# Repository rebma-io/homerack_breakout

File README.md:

# STM32 Morpho Expansion Board for HOMERACK

Not really ready to talk about the project, but it was inspired by the
[kha](https://github.com/kiu/kha) project by WHO? This is just the beginning of the project, but I
decided to start with a STM32 Nucleo-64 board and work from there. This
is just a breakout for a bunch of the IO to a lot of JST PH connectors.

You can see the schematic and PCB layout
[online](https://kicanvas.org/?github=https%3A%2F%2Fgithub.com%2Frebma-io%2Fhomerack_breakout)
thanks to the super-brilliant [Stargirl](https://github.com/theacodes).

## License
The license is [CC0](https://creativecommons.org/public-domain/cc0/),
which means, effectively, do whatever you want.

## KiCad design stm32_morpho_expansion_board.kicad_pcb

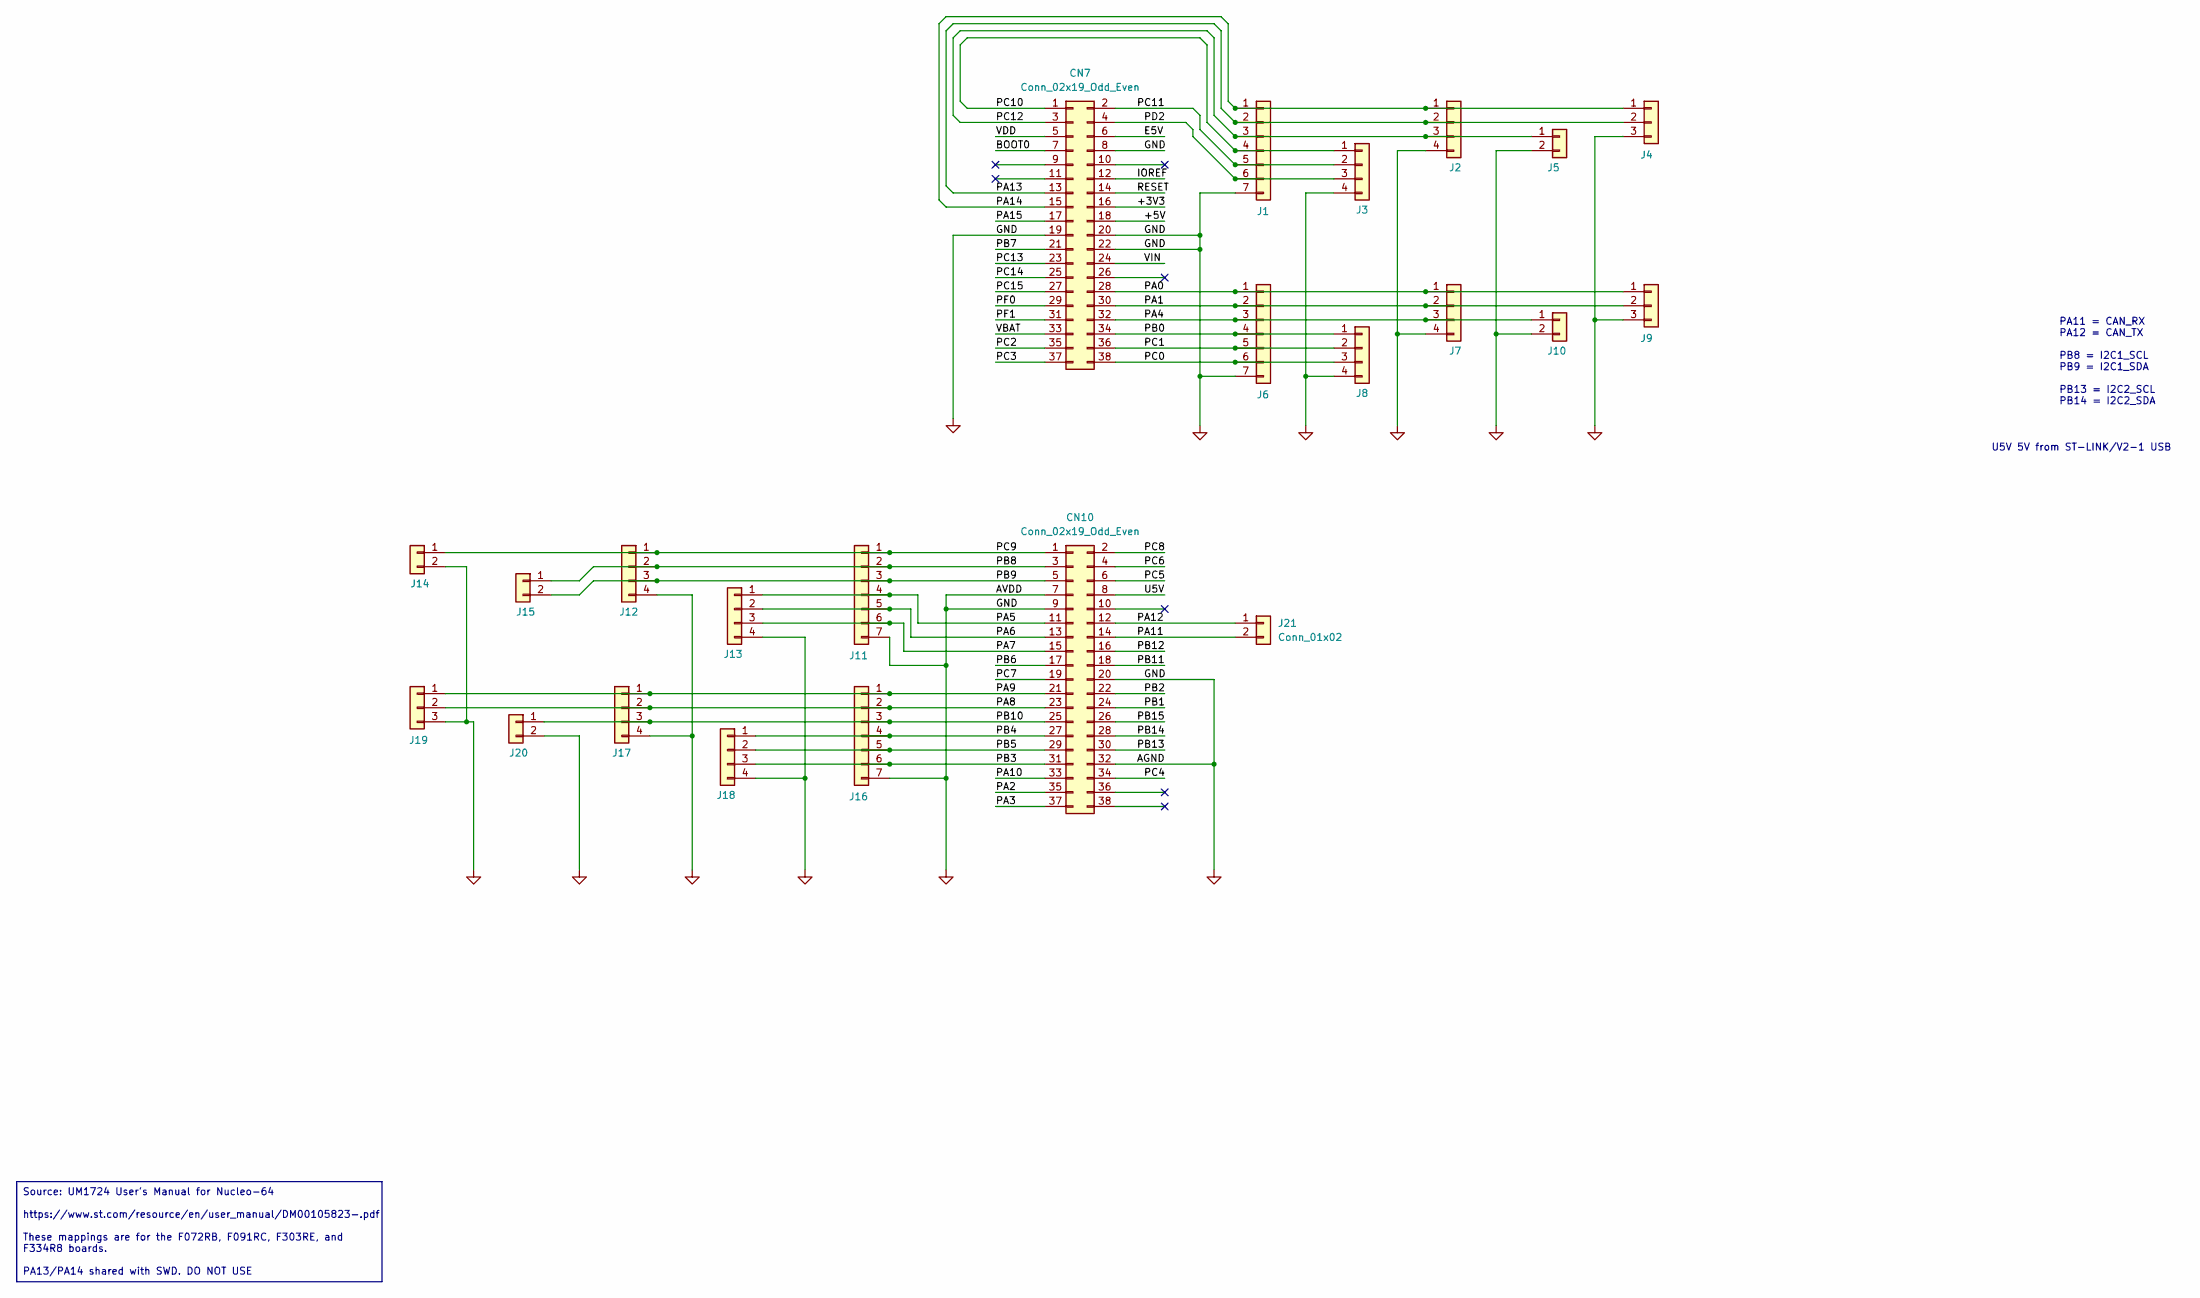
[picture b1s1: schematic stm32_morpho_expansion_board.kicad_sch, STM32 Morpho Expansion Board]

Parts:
CN7, CN10: Conn_02x19_Odd_Even; PinSocket_2x19_P2.54mm_Vertical
J1, J6, J11, J16: Conn_01x07; JST_PH_B7B-PH-K_1x07_P2.00mm_Vertical
J2, J3, J7, J8, J12, J13, J17, J18: Conn_01x04; JST_PH_B4B-PH-K_1x04_P2.00mm_Vertical
J4, J9, J19: Conn_01x03; JST_PH_B3B-PH-K_1x03_P2.00mm_Vertical
J5, J10, J14, J15, J20, J21: Conn_01x02; JST_PH_B2B-PH-K_1x02_P2.00mm_Vertical

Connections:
/+3V3: CN7.16
/+5V: CN7.18
/BOOT0: CN7.7
/E5V: CN7.6
/IOREF: CN7.12
/PA0: CN7.28, J6.1, J7.1, J9.1
/PA1: CN7.30, J6.2, J7.2, J9.2
/PA2: CN10.35
/PA3: CN10.37
/PA4: CN7.32, J6.3, J7.3, J10.1
/PA5: CN10.11, J11.4, J13.1
/PA6: CN10.13, J11.5, J13.2
/PA7: CN10.15, J11.6, J13.3
/PA8: CN10.23, J16.2, J17.2, J19.2
/PA9: CN10.21, J16.1, J17.1, J19.1
/PA10: CN10.33
/PA11: CN10.14, J21.2
/PA12: CN10.12, J21.1
/PA13: CN7.13, J1.2, J2.2, J4.2
/PA14: CN7.15, J1.1, J2.1, J4.1
/PA15: CN7.17
/PB0: CN7.34, J6.4, J8.1
/PB1: CN10.24
/PB2: CN10.22
/PB3: CN10.31, J16.6, J18.3
/PB4: CN10.27, J16.4, J18.1
/PB5: CN10.29, J16.5, J18.2
/PB6: CN10.17
/PB7: CN7.21
/PB8: CN10.3, J11.2, J12.2, J15.1
/PB9: CN10.5, J11.3, J12.3, J15.2
/PB10: CN10.25, J16.3, J17.3, J20.1
/PB11: CN10.18
/PB12: CN10.16
/PB13: CN10.30
/PB14: CN10.28
/PB15: CN10.26
/PC0: CN7.38, J6.6, J8.3
/PC1: CN7.36, J6.5, J8.2
/PC2: CN7.35
/PC3: CN7.37
/PC4: CN10.34
/PC5: CN10.6
/PC6: CN10.4
/PC7: CN10.19
/PC8: CN10.2
/PC9: CN10.1, J11.1, J12.1, J14.1
/PC10: CN7.1, J1.4, J3.1
/PC11: CN7.2, J1.5, J3.2
/PC12: CN7.3, J1.3, J2.3, J5.1
/PC13: CN7.23
/PC14: CN7.25
/PC15: CN7.27
/PD2: CN7.4, J1.6, J3.3
/PF0: CN7.29
/PF1: CN7.31
/RESET: CN7.14
/U5V: CN10.8
/VBAT: CN7.33
/VDD: CN7.5
/VIN: CN7.24
GND: CN7.8, CN7.19, CN7.20, CN7.22, CN10.7, CN10.9, CN10.20, CN10.32, J1.7, J2.4, J3.4, J4.3, J5.2, J6.7, J7.4, J8.4, J9.3, J10.2, J11.7, J12.4, J13.4, J14.2, J16.7, J17.4, J18.4, J19.3, J20.2

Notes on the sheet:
Source: UM1724 User's Manual for Nucleo-64 https://www.st.com/resource/en/user_manual/DM00105823-.pdf These mappings are for the F072RB, F091RC, F303RE, and F334R8 boards. PA13/PA14 shared with SWD. DO NOT USE
PA11 = CAN_RX PA12 = CAN_TX PB8 = I2C1_SCL PB9 = I2C1_SDA PB13 = I2C2_SCL PB14 = I2C2_SDA
U5V 5V from ST-LINK/V2-1 USB

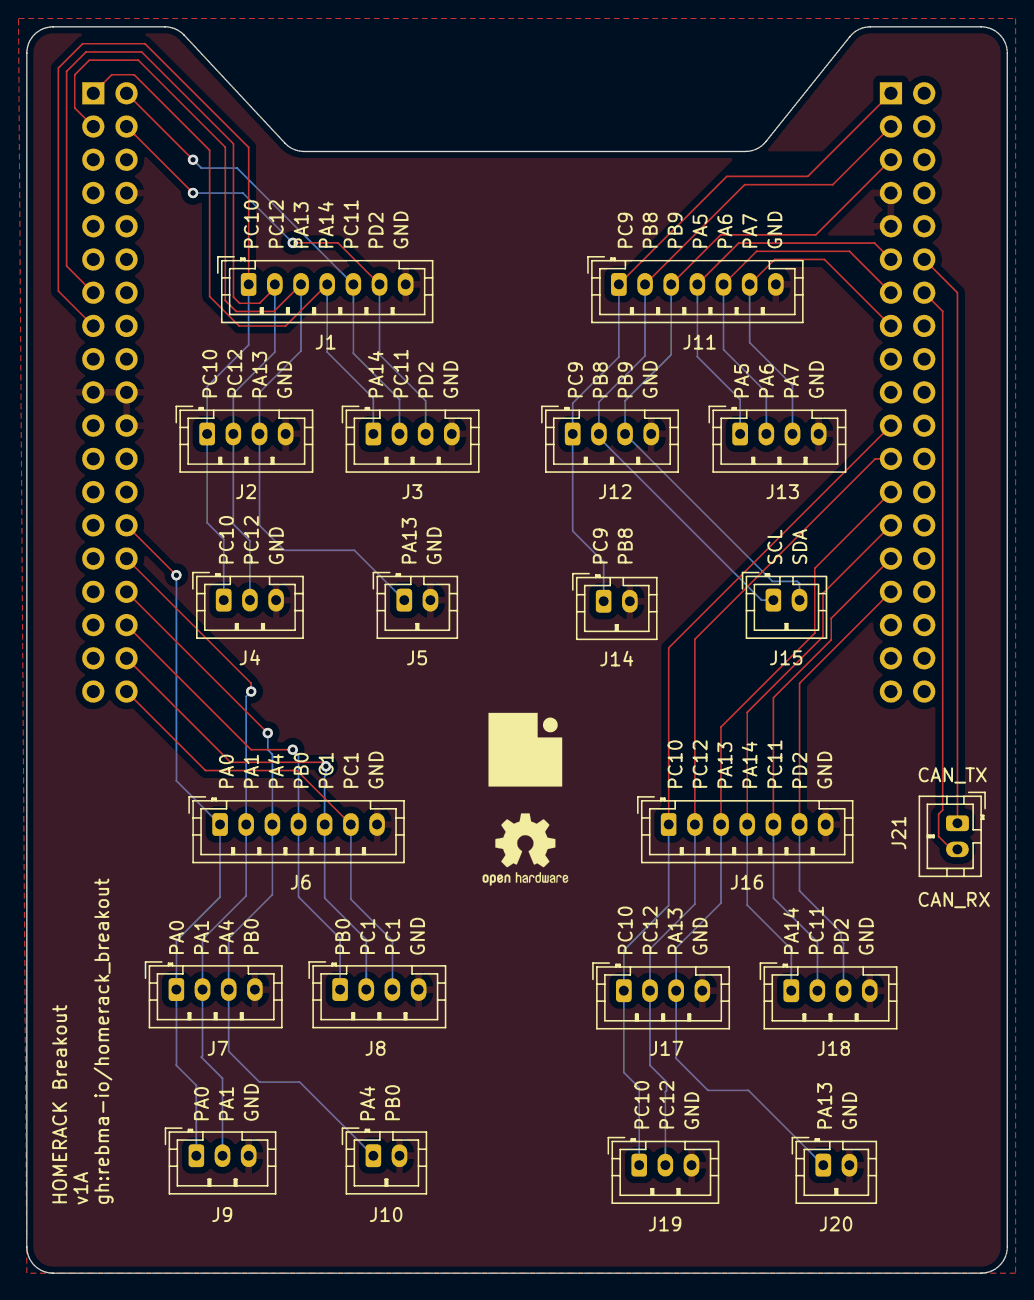
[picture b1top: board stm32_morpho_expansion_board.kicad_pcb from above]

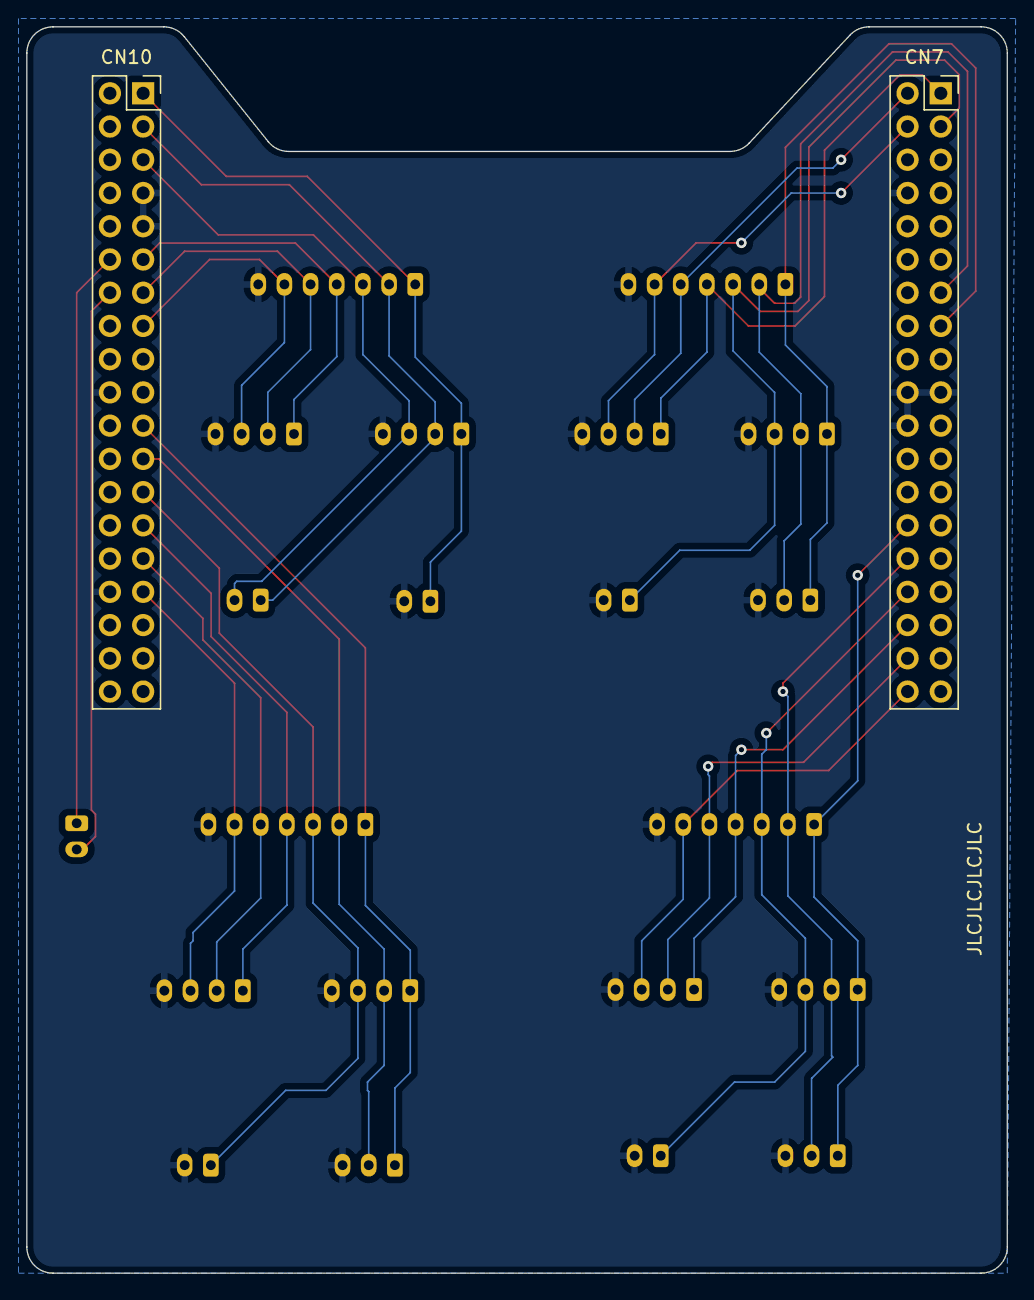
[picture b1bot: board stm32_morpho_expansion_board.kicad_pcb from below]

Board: 2 copper layers, 74.9 x 95.3 mm, 23 parts (2 on the bottom side), 27 nets.

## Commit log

2024-04-17 Initial version of the baord.
2024-04-17 Ignore noisy KiCad files
2024-04-17 Quick README
